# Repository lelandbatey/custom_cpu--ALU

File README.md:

Arithmetic Logic Unit (ALU)
===========================

This repo contains PCB designs for the third component of Ben Eater's
educational 8-bit CPU, the arithmetic logic unit or ALU. You can [watch Mr.
Eaters *fantastic* series on designing and building this CPU on his Youtube
channel.](https://www.youtube.com/user/eaterbc/videos)

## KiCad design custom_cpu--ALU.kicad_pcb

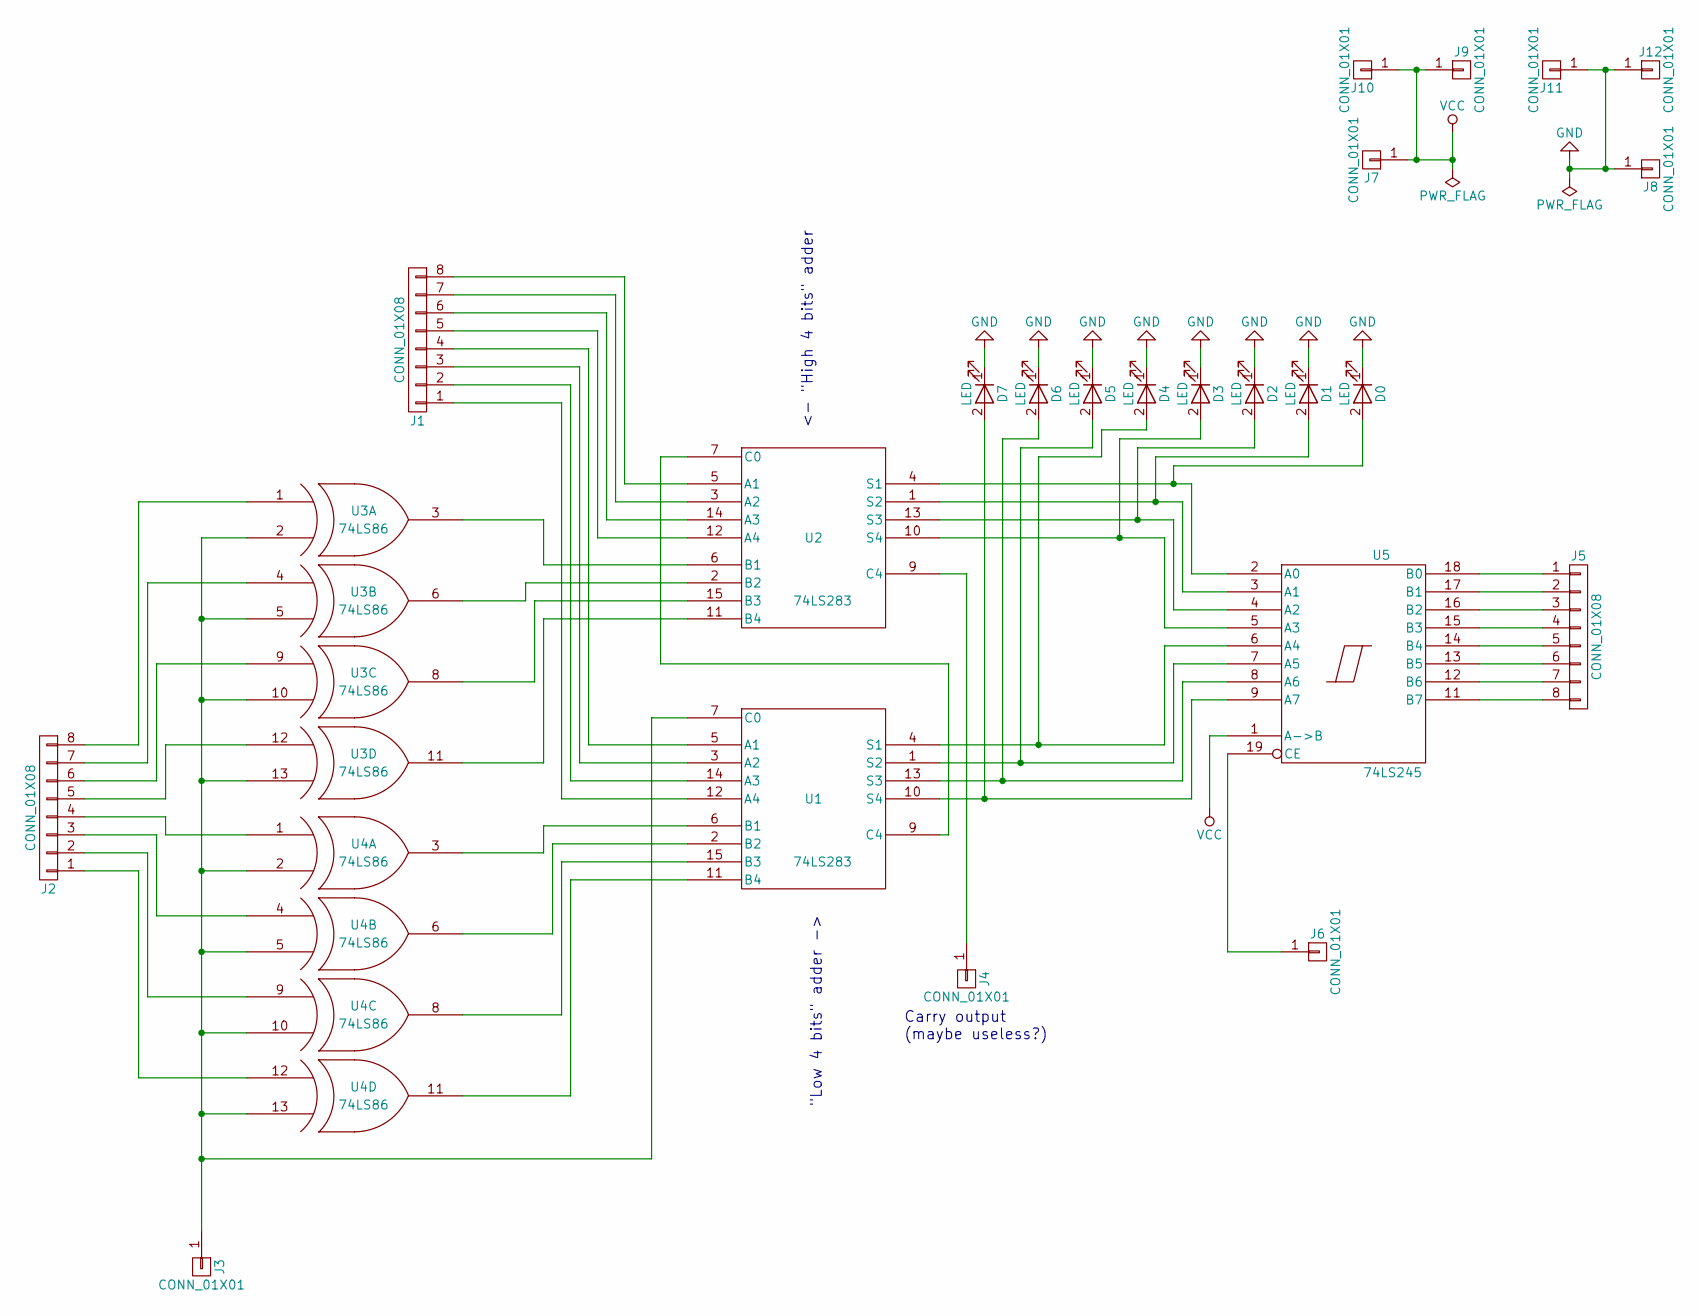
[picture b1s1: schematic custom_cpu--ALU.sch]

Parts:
D0, D1, D2, D3, D4, D5, D6, D7: LED; LED_D5.0mm
J1, J2, J5: CONN_01X08; Pin_Header_Straight_1x08_Pitch2.54mm
J3, J4, J6, J7, J8: CONN_01X01; Pin_Header_Straight_1x01_Pitch2.54mm
J9, J10, J11, J12: CONN_01X01; SolderWirePad_single_SMD_5x10mm
U1, U2: 74LS283; DIP-16_W7.62mm_Socket
U3, U4: 74LS86; DIP-14_W7.62mm_Socket
U5: 74LS245; DIP-20_W7.62mm_Socket

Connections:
GND: D0.1 (K), D1.1 (K), D2.1 (K), D3.1 (K), D4.1 (K), D5.1 (K), D6.1 (K), D7.1 (K), J8.1, J11.1, J12.1, U1.8 (GND), U2.8 (GND), U3.7 (GND), U4.7 (GND), U5.10 (GND)
unnamed: D0.2 (A), U2.4 (S1), U5.2 (A0)
unnamed: D1.2 (A), U2.1 (S2), U5.3 (A1)
unnamed: D2.2 (A), U2.13 (S3), U5.4 (A2)
unnamed: D3.2 (A), U2.10 (S4), U5.5 (A3)
unnamed: D4.2 (A), U1.4 (S1), U5.6 (A4)
unnamed: D5.2 (A), U1.1 (S2), U5.7 (A5)
unnamed: D6.2 (A), U1.13 (S3), U5.8 (A6)
unnamed: D7.2 (A), U1.10 (S4), U5.9 (A7)
unnamed: J1.1, U1.12 (A4)
unnamed: J1.2, U1.14 (A3)
unnamed: J1.3, U1.3 (A2)
unnamed: J1.4, U1.5 (A1)
unnamed: J1.5, U2.12 (A4)
unnamed: J1.6, U2.14 (A3)
unnamed: J1.7, U2.3 (A2)
unnamed: J1.8, U2.5 (A1)
unnamed: J2.1, U4.12 (IN1)
unnamed: J2.2, U4.9 (IN1)
unnamed: J2.3, U4.4 (IN1)
unnamed: J2.4, U4.1 (IN1)
unnamed: J2.5, U3.12 (IN1)
unnamed: J2.6, U3.9 (IN1)
unnamed: J2.7, U3.4 (IN1)
unnamed: J2.8, U3.1 (IN1)
unnamed: J3.1, U1.7 (C0), U3.2 (IN2), U3.5 (IN2), U3.10 (IN2), U3.13 (IN2), U4.2 (IN2), U4.5 (IN2), U4.10 (IN2), U4.13 (IN2)
unnamed: J4.1, U2.9 (C4)
unnamed: J5.1, U5.18 (B0)
unnamed: J5.2, U5.17 (B1)
unnamed: J5.3, U5.16 (B2)
unnamed: J5.4, U5.15 (B3)
unnamed: J5.5, U5.14 (B4)
unnamed: J5.6, U5.13 (B5)
unnamed: J5.7, U5.12 (B6)
unnamed: J5.8, U5.11 (B7)
unnamed: J6.1, U5.19 (CE)
unnamed: U1.2 (B2), U4.6 (OUT)
unnamed: U1.6 (B1), U4.3 (OUT)
unnamed: U1.9 (C4), U2.7 (C0)
unnamed: U1.11 (B4), U4.11 (OUT)
unnamed: U1.15 (B3), U4.8 (OUT)
unnamed: U2.2 (B2), U3.6 (OUT)
unnamed: U2.6 (B1), U3.3 (OUT)
unnamed: U2.11 (B4), U3.11 (OUT)
unnamed: U2.15 (B3), U3.8 (OUT)
VCC: J7.1, J9.1, J10.1, U1.16 (VCC), U2.16 (VCC), U3.14 (VCC), U4.14 (VCC), U5.1 (A->B), U5.20 (VCC)

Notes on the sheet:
"Low 4 bits" adder ->
<- "High 4 bits" adder
Carry output (maybe useless?)

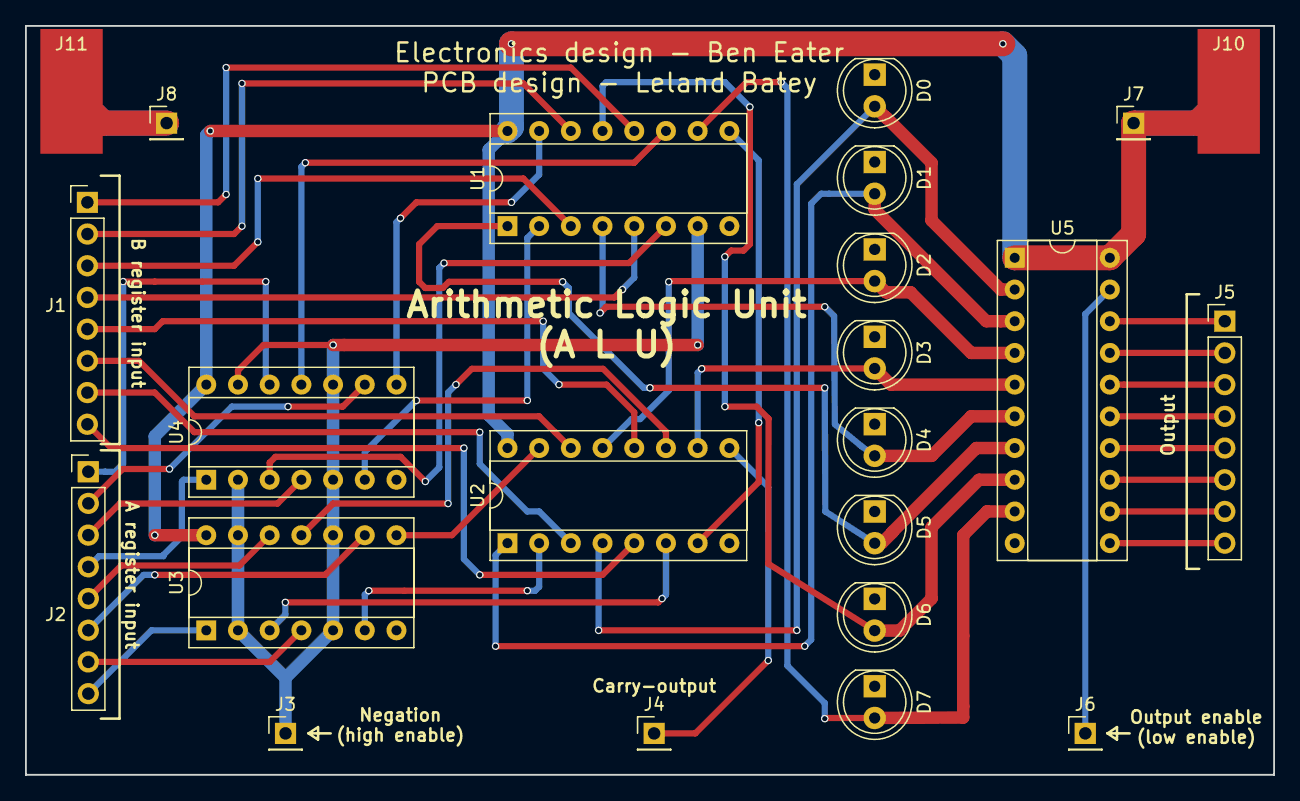
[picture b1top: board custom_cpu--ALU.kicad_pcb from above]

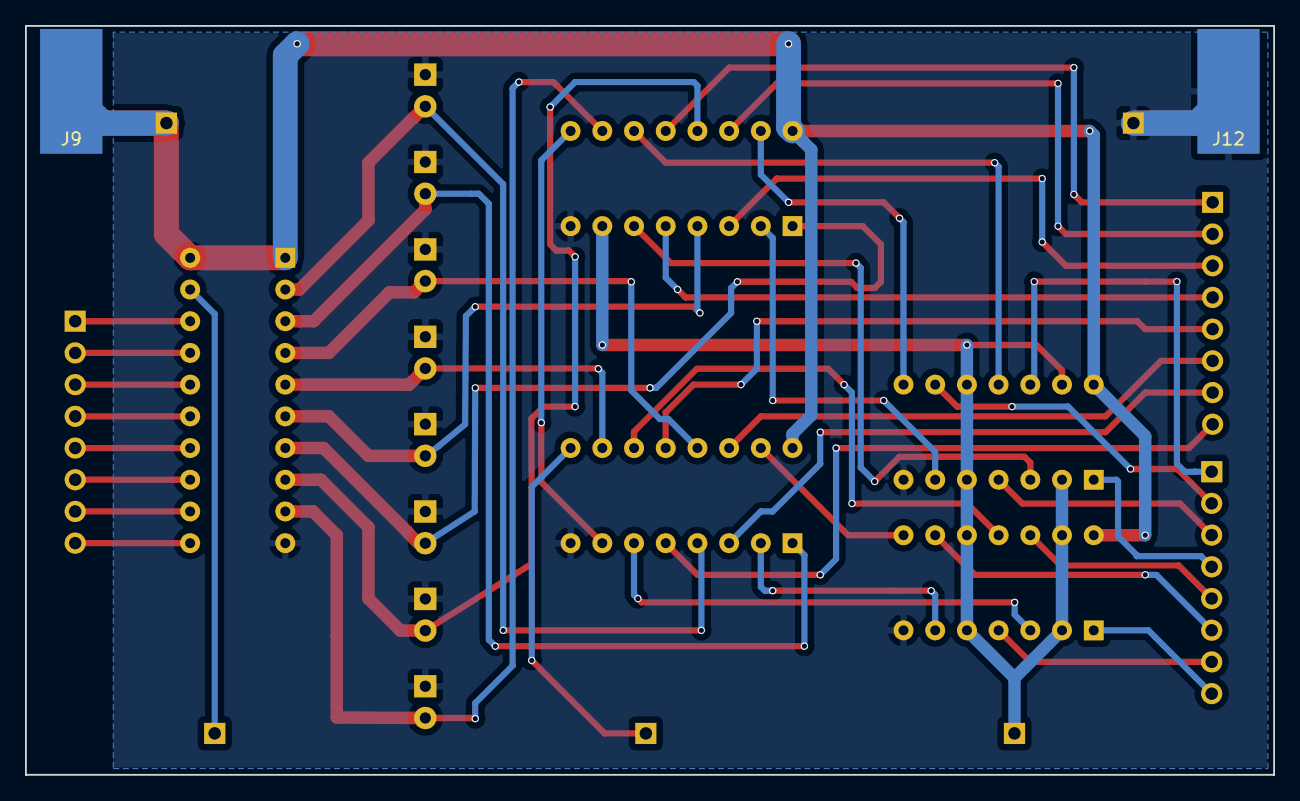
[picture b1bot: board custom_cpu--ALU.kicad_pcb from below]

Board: 2 copper layers, 100.0 x 60.0 mm, 25 parts (2 on the bottom side), 46 nets.

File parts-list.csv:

ALU Parts List,,,,,
Part Name,Count,Unit Price,Total Price,,Total Price of ALL Materials
LED (yellow),8,$0.20,$1.60,,$9.87
"Pin header, 1x8",3,$0.86,$2.58,,
20 Pin DIP socket,1,$0.24,$0.24,,
16 Pin DIP socket,2,$0.18,$0.36,,
14 Pin DIP socket,2,$0.21,$0.42,,
74LS283 (4-bit adder),2,$1.38,$2.76,,
74LS86 (XOR),2,$0.52,$1.04,,
74LS245 (bus transceiver),1,$0.87,$0.87,,

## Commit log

2017-06-01 Fix touching trace
2017-06-01 fix a couple more touching traces
2017-06-03 Add power labels
2017-06-03 Update ALU renders
2017-06-03 Fix input register labels
2017-06-03 Add parts list and cost of materials
